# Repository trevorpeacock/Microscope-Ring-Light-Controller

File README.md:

# PWM controller for microscope ringlight

very rough project to make an ATTiny85 powered PWM controller to run 24V ringlight

* MicroscopeLightPCB is a kicad project with schematic and rough board layout.
  * Board was manufactured on protoboard, PCB layout helped for hand routing enamel jumper wire to connect components.
* MicroscopeLightFW is an Arduino IDE project to program the Atmel.

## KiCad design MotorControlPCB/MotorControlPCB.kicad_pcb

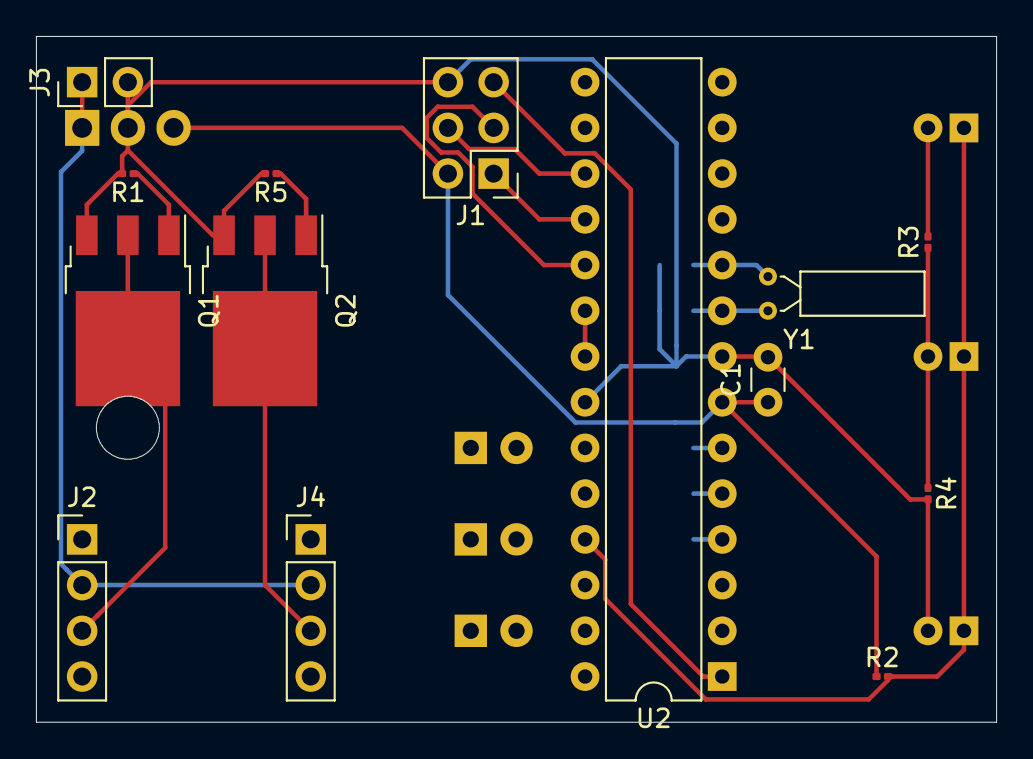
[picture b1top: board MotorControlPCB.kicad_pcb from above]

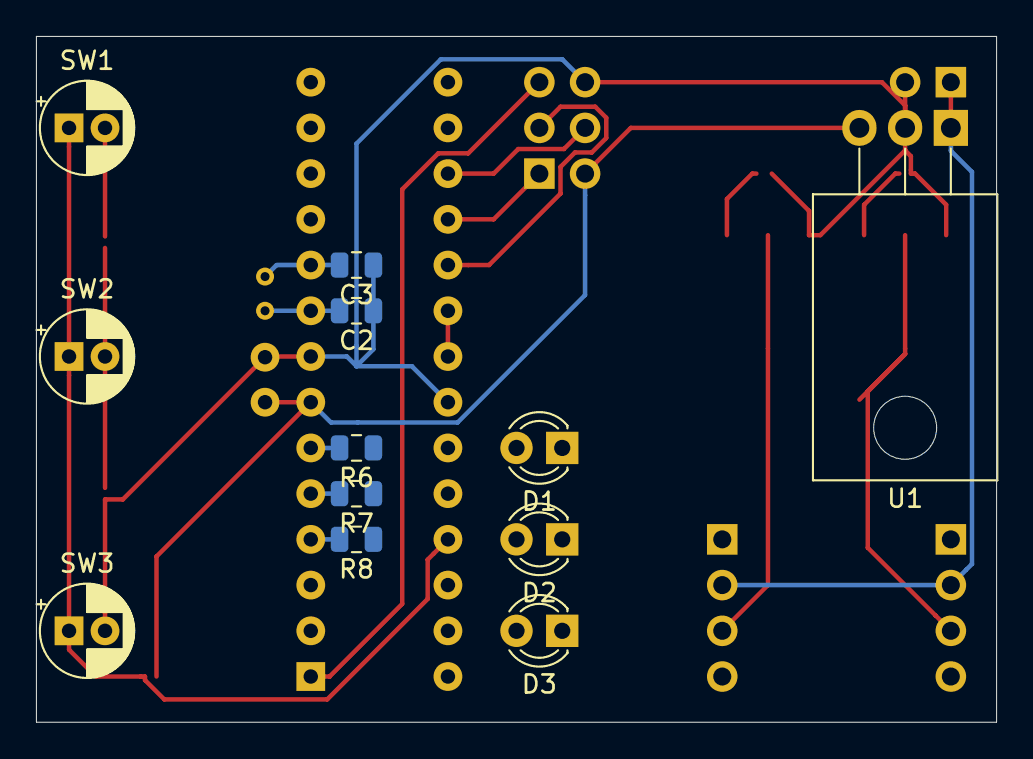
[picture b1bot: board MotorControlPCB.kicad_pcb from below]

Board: 2 copper layers, 53.3 x 38.1 mm, 26 parts (12 on the bottom side), 26 nets.

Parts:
C1: C_Small; C_Disc_D3.0mm_W1.6mm_P2.50mm
C2, C3: C_Small; C_0805_2012Metric
D1, D2, D3: LED; LED_D3.0mm
J1: Conn_02x03_Odd_Even; PinHeader_2x03_P2.54mm_Vertical
J2, J4: Conn_01x04; PinHeader_1x04_P2.54mm_Vertical
J3: Conn_01x02; PinHeader_1x02_P2.54mm_Vertical
Q1, Q2: Q_NMOS_GDS; TO-252-3_TabPin2
R1, R2, R3, R4, R5: R_Small; R_0201_0603Metric
R6, R7, R8: R_Small; R_0805_2012Metric
SW1, SW2, SW3: SW_Push; CP_Radial_D5.0mm_P2.00mm
U1: L7805; TO-220-3_Horizontal_TabDown
U2: ATmega328P-PU; DIP-28_W7.62mm
Y1: Crystal_Small; Crystal_C26-LF_D2.1mm_L6.5mm_Horizontal

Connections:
/5V: C1.1, J1.2, R2.1, U1.3, U2.7, U2.20, U2.21
/12V: J2.2, J3.1, J4.2, U1.1
/Buttons: R2.2, SW1.1, SW2.1, SW3.1, U2.25
/MISO: J1.1, U2.18
/MOSI: J1.4, U2.17
/MOT1_En: Q1.1, R1.1, U2.27
/MOT1_GND: J2.3, Q1.2
/MOT1_PWM: J2.4, U2.15
/MOT1_Tach: J2.1, U2.23
/MOT2_En: Q2.1, R5.1, U2.26
/MOT2_GND: J4.3, Q2.2
/MOT2_PWM: J4.4, U2.16
/MOT2_Tach: J4.1, U2.24
/RST: J1.5, U2.1
/SCK: J1.3, U2.19
GND: C1.2, C2.1, C3.1, D1.1, D2.1, D3.1, J1.6, J3.2, Q1.3, Q2.3, R1.2, R4.2, R5.2, SW3.2, U1.2, U2.8, U2.22
unnamed: C2.2, U2.9, Y1.1
unnamed: C3.2, U2.10, Y1.2
unnamed: D1.2, R6.1
unnamed: D2.2, R7.1
unnamed: D3.2, R8.1
unnamed: R3.1, R4.1, SW2.2
unnamed: R3.2, SW1.2
unnamed: R6.2, U2.6
unnamed: R7.2, U2.5
unnamed: R8.2, U2.4

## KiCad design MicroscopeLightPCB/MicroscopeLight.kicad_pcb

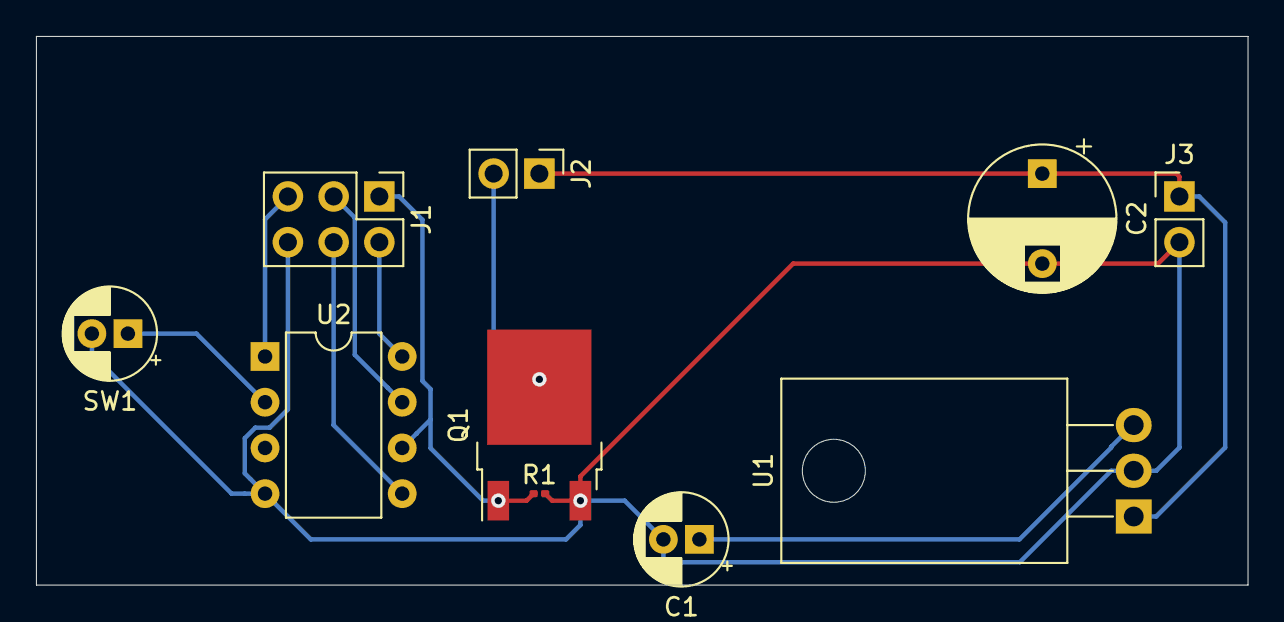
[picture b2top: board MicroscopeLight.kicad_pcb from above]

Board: 2 copper layers, 67.3 x 30.5 mm, 10 parts (0 on the bottom side), 9 nets.

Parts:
C1: C_Small; CP_Radial_D5.0mm_P2.00mm
C2: C_Small; CP_Radial_D8.0mm_P5.00mm
J1: Conn_02x03_Odd_Even; PinHeader_2x03_P2.54mm_Vertical
J2, J3: Conn_01x02; PinHeader_1x02_P2.54mm_Vertical
Q1: Q_NMOS_GDS; TO-252-3_TabPin2
R1: R_Small; R_0201_0603Metric
SW1: SW_Push; CP_Radial_D5.0mm_P2.00mm
U1: L7805; TO-220-3_Horizontal_TabDown
U2: ATtiny85-20PU; DIP-8_W7.62mm

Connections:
/5V: C1.1, J1.2, U1.3, U2.8
/24V: C2.1, J2.1, J3.1, U1.1
/LED_En: J1.1, Q1.1, R1.1, U2.6
/MOSI: J1.4, U2.5
/RST: J1.5, U2.1
/SCK: J1.3, U2.7
GND: C1.2, C2.2, J1.6, J3.2, Q1.3, R1.2, SW1.2, U1.2, U2.4
unnamed: J2.2, Q1.2
unnamed: SW1.1, U2.2

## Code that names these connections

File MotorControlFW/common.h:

#include "eeprom.h"

#define LED1_PIN 2
#define LED2_PIN 3
#define LED3_PIN 4
#define BUTTON_PIN A2
#define MOT1_EN_PIN A4
#define MOT2_EN_PIN A3
#define MOT1_PWM_PIN 9
#define MOT2_PWM_PIN 10
#define MOT1_TACH_PIN A0
#define MOT2_TACH_PIN A1

#define BUTTON_READINGS 8

const word PWM_FREQ_HZ = 20000; //Adjust this value to adjust the frequency
const word TCNT1_TOP = F_CPU/(2*PWM_FREQ_HZ);

class ButtonManager
{
  public:
    ButtonManager() {
      for(uint8_t i = 0; i < BUTTON_READINGS; i++) {
        _btn_laststate[i]=1023;
      }
      _btn_laststate_count = 0;
      _btn_down = false;
      _last_trigger = millis();
    }
    int readval() {
      int btnstate;
      btnstate = analogRead(BUTTON_PIN);
      _btn_laststate[_btn_laststate_count++]=btnstate;
      if(_btn_laststate_count == BUTTON_READINGS) _btn_laststate_count=0;
      return btnstate;
    }
    int avgval() {
      int total = 0;
      for(uint8_t i = 0; i < BUTTON_READINGS; i++) {
        total += _btn_laststate[i];
      }
      return total / BUTTON_READINGS;
    }
    uint8_t check() {
      int btnstate = this->readval();
      if(abs(this->avgval() - btnstate) > 10) return 0;
      if(btnstate < 256) return 1;
      if(btnstate < 600) return 2;
      if(btnstate < 800) return 3;
      return 0;
    }
    uint8_t check_repeat(bool rpt1, bool rpt2, bool rpt3) {
      int btnstate = this->check();
      //no button pressed
      if(btnstate==0) {
        _btn_down = false;
        return 0;
      }
      
      bool new_press = not _btn_down;
      _btn_down = true;
      if(millis() - _last_down_state < 50) new_press = false;
      _last_down_state = millis();
      
      if(btnstate == 1 && not rpt1) {
        if(new_press) return btnstate;
        return 0;
      }
      if(btnstate == 2 && not rpt2) {
        if(new_press) return btnstate;
        return 0;
      }
      if(btnstate == 3 && not rpt3) {
        if(new_press) return btnstate;
        return 0;
      }
      if(millis() - _last_trigger > 50) {
        _last_trigger = millis();
        return btnstate;
      }
      return 0;
    }
    void wait_for_release() {
      unsigned long last_press = millis();
      while(millis() - last_press < 50) {
        if(this->check()) last_press = millis();
      }
    }
  private:
    int _btn_laststate[BUTTON_READINGS];
    uint8_t _btn_laststate_count;
    bool _btn_down;
    unsigned long _last_trigger;
    unsigned long _last_down_state;
};

class MotorControl
{
  public:
    MotorControl(uint8_t mot) {
      _mot = mot;
      if(_mot==0) {
        _en_pin = MOT1_EN_PIN;
        _pwm_pin = MOT1_PWM_PIN;
        _tach_pin = MOT1_TACH_PIN;
        _ocr = &OCR1A;
      } else if(_mot==1) {
        _en_pin = MOT2_EN_PIN;
        _pwm_pin = MOT2_PWM_PIN;
        _tach_pin = MOT2_TACH_PIN;
        _ocr = &OCR1B;
      }
    }
    int setup() {
      pinMode(_en_pin, OUTPUT);
      pinMode(_pwm_pin, OUTPUT);
      pinMode(_tach_pin, INPUT);
    
      // Clear Timer1 control and count registers
      TCCR1A = 0;
      TCCR1B = 0;
      TCNT1  = 0;
    
      // Set Timer1 configuration
      // COM1A(1:0) = 0b10   (Output A clear rising/set falling)
      // COM1B(1:0) = 0b00   (Output B normal operation)
      // WGM(13:10) = 0b1010 (Phase correct PWM)
      // ICNC1      = 0b0    (Input capture noise canceler disabled)
      // ICES1      = 0b0    (Input capture edge select disabled)
      // CS(12:10)  = 0b001  (Input clock select = clock/1)
      
      TCCR1A |= (1 << COM1A1) | (1 << COM1B1) | (1 << WGM11);
      TCCR1B |= (1 << WGM13) | (1 << CS10);
      ICR1 = TCNT1_TOP;
    }
    void set(int spd) {
      if(spd<0) spd=0;
      if(spd>101) spd=101;
      _cur_speed = spd;
      if(_cur_speed==0) {
        *_ocr = (word) 0;
        digitalWrite(_en_pin, LOW);
        return;
      }
      *_ocr = (word) ((_cur_speed-1)*TCNT1_TOP)/100;
      digitalWrite(_en_pin, HIGH);
    }
    uint8_t get_speed() {
      return _cur_speed;
    }
  private:
    uint8_t _mot;
    uint8_t _en_pin;
    uint8_t _pwm_pin;
    uint8_t _tach_pin;
    uint16_t *_ocr;
    uint8_t _cur_speed;
};

ButtonManager button_manager;
MotorControl motor1_control(0);
MotorControl motor2_control(1);

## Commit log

2020-09-06 Project finished... for now, board built and working
2020-09-06 Add photo
2020-09-12 add programming notes
2020-11-01 Add motor controller
